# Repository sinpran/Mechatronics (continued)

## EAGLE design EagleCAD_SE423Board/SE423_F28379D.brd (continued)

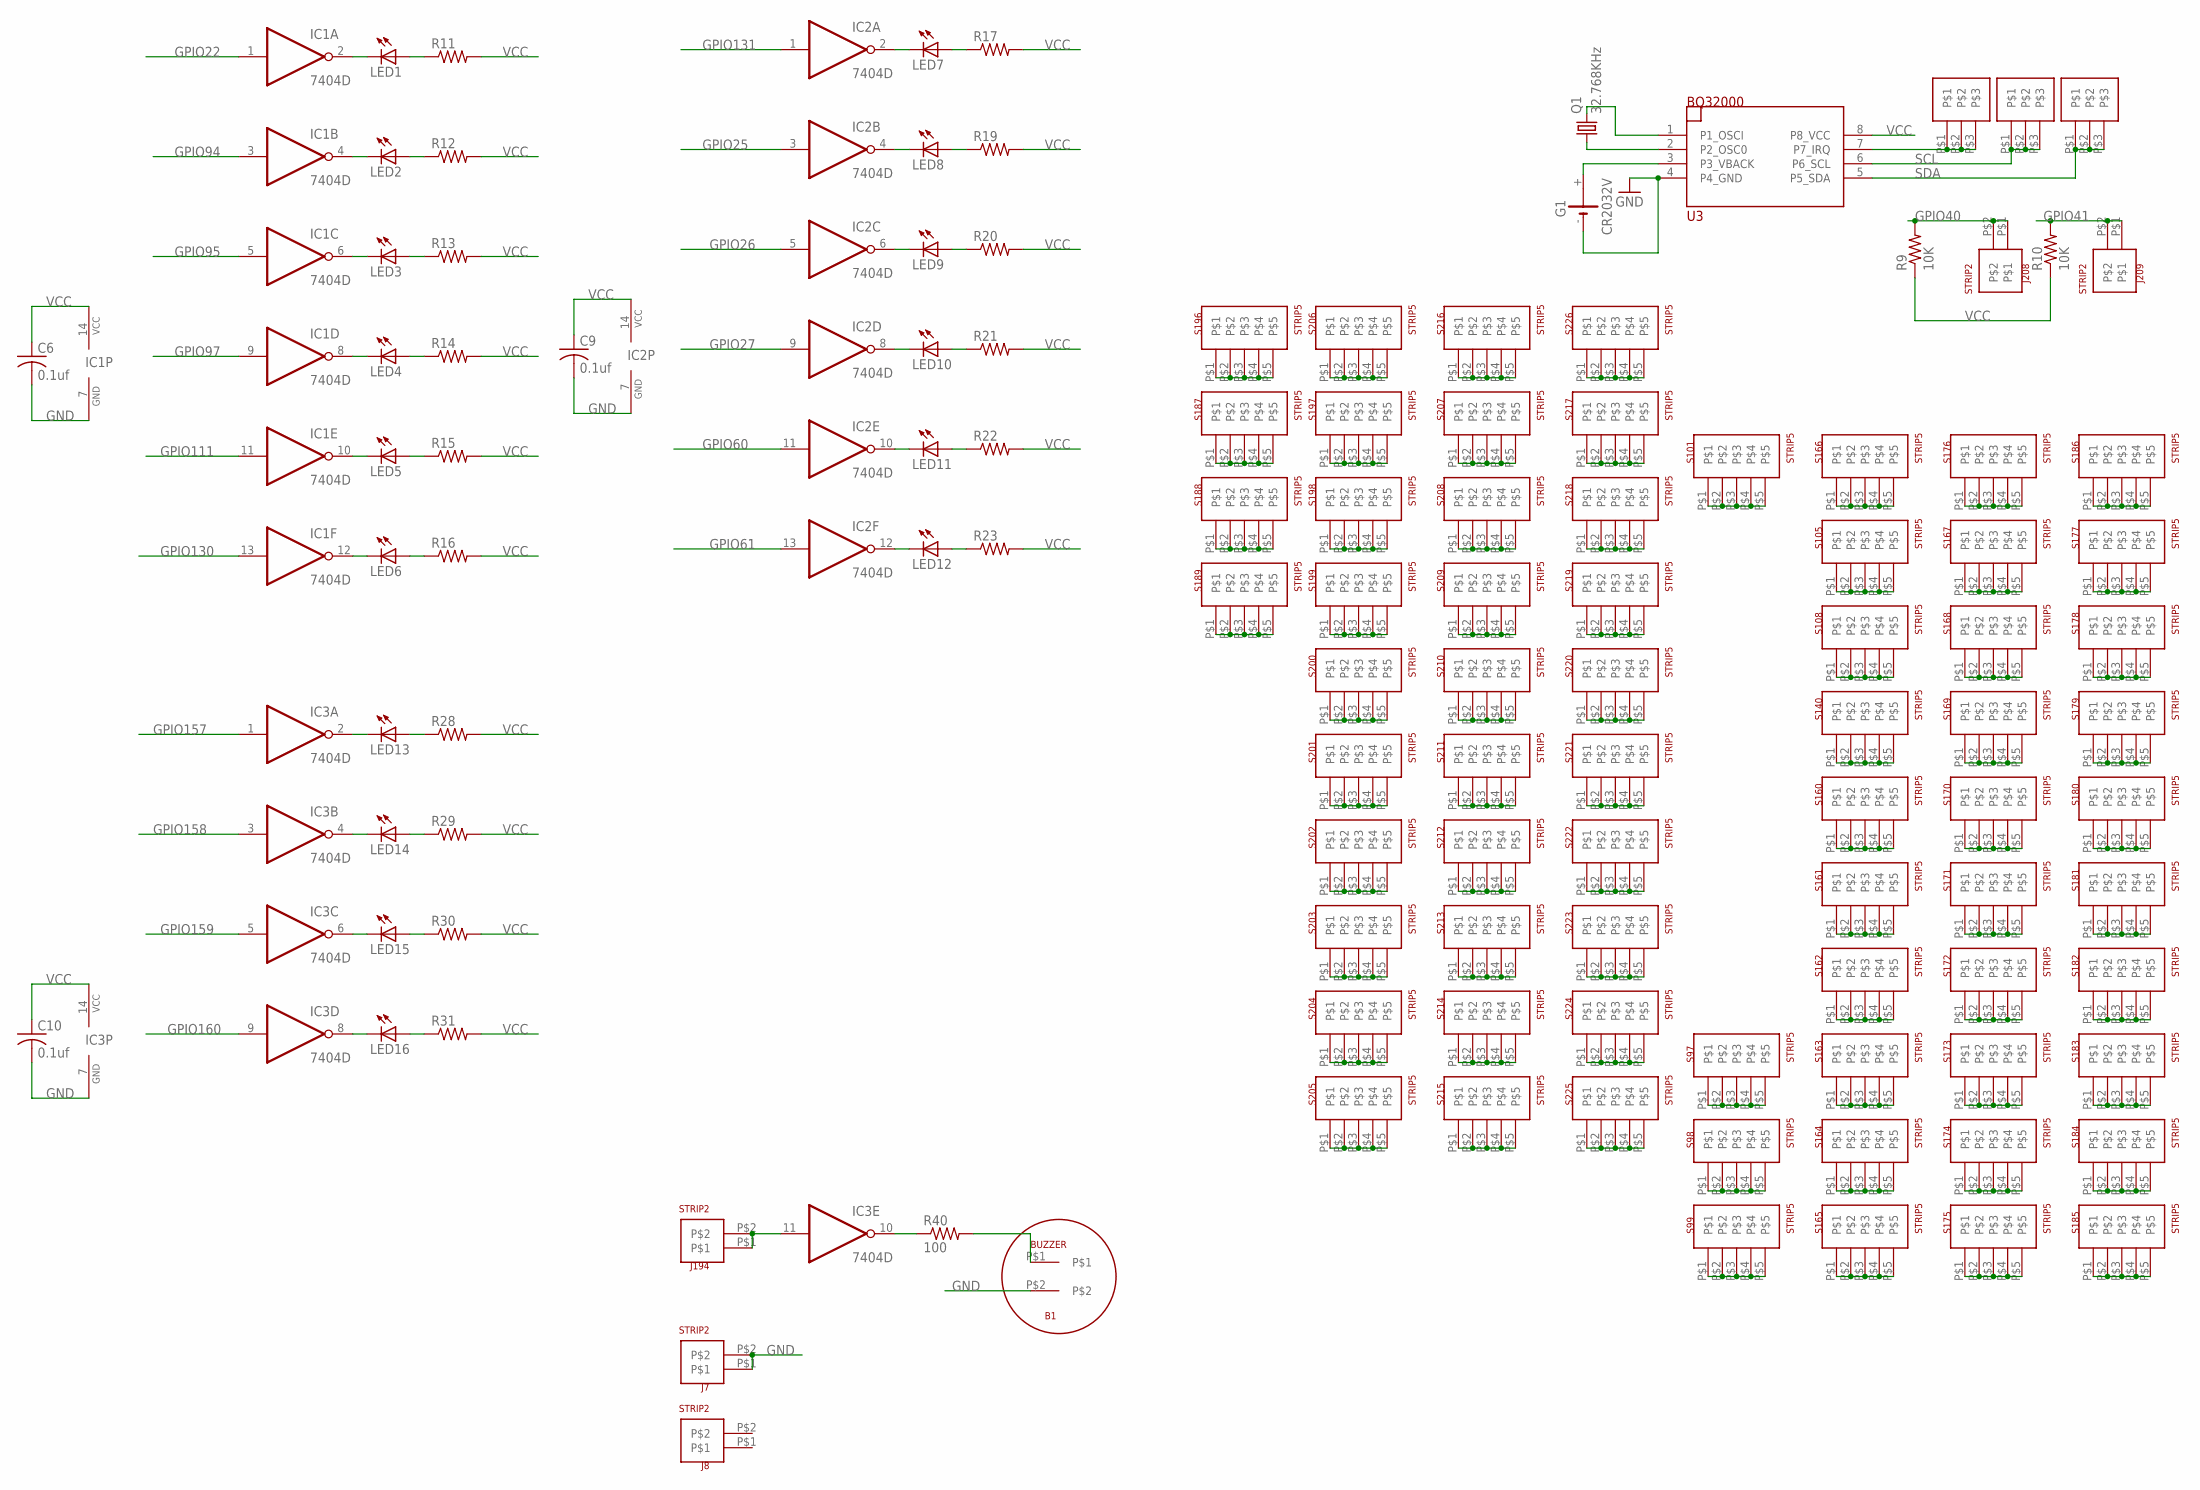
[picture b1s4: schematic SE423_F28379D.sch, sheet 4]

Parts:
B1: BUZZER
C6, C9, C10: 0.1uf; C1206
G1: CR2032V
IC1, IC2, IC3: 7404D; SO14
J1, J2, J3: STRIP3
J7, J8, J194, J208, J209: STRIP2
LED1, LED2, LED3, LED4, LED5, LED6, LED7, LED8, LED9, LED10, LED11, LED12, LED13, LED14, LED15, LED16: LEDCHIPLED_1206; CHIPLED_1206
Q1: 32.768KHz; TC26H
R9, R10: 10K; R1206
R11, R12, R13, R14, R15, R16, R17, R19, R20, R21, R22, R23, R28, R29, R30, R31: R-US_R1206; R1206
R40: 100; R1206
S97, S98, S99, S101, S105, S108, S140, S160, S161, S162, S163, S164, S165, S166, S167, S168, S169, S170, S171, S172, S173, S174, S175, S176, S177, S178, S179, S180, S181, S182, S183, S184, S185, S186, S187, S188, S189, S196, S197, S198, S199, S200, S201, S202, S203, S204, S205, S206, S207, S208, S209, S210, S211, S212, S213, S214, S215, S216, S217, S218, S219, S220, S221, S222, S223, S224, S225, S226: STRIP5
U3: BQ32000; SO08

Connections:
GND: B1.P$2, C6.2, C9.2, C10.2, G1.-, IC1.7 (GND), IC2.7 (GND), IC3.7 (GND), J7.P$1, J7.P$2, U3.4 (P4_GND); also elsewhere on the board
GPIO22: IC1.1 (I); also elsewhere on the board
GPIO25: IC2.3 (I); also elsewhere on the board
GPIO26: IC2.5 (I); also elsewhere on the board
GPIO27: IC2.9 (I); also elsewhere on the board
GPIO40: J208.P$1, J208.P$2, R9.2; also elsewhere on the board
GPIO41: J209.P$1, J209.P$2, R10.2; also elsewhere on the board
GPIO60: IC2.11 (I); also elsewhere on the board
GPIO61: IC2.13 (I); also elsewhere on the board
GPIO94: IC1.3 (I); also elsewhere on the board
GPIO95: IC1.5 (I); also elsewhere on the board
GPIO97: IC1.9 (I); also elsewhere on the board
GPIO111: IC1.11 (I); also elsewhere on the board
GPIO130: IC1.13 (I); also elsewhere on the board
GPIO131: IC2.1 (I); also elsewhere on the board
GPIO157: IC3.1 (I); also elsewhere on the board
GPIO158: IC3.3 (I); also elsewhere on the board
GPIO159: IC3.5 (I); also elsewhere on the board
GPIO160: IC3.9 (I); also elsewhere on the board
unnamed: IC3.10 (O), R40.1
unnamed: B1.P$1, R40.2
unnamed: Q1.1, U3.2 (P2_OSC0)
unnamed: Q1.2, U3.1 (P1_OSCI)
unnamed: J1.P$1, J1.P$2, J1.P$3, U3.7 (P7_IRQ)
unnamed: G1.+, U3.3 (P3_VBACK)
unnamed: IC2.2 (O), LED7.C
unnamed: LED7.A, R17.1
unnamed: IC2.4 (O), LED8.C
unnamed: LED8.A, R19.1
unnamed: IC2.6 (O), LED9.C
unnamed: S97.P$1, S97.P$2, S97.P$3, S97.P$4, S97.P$5
unnamed: S98.P$1, S98.P$2, S98.P$3, S98.P$4, S98.P$5
unnamed: S99.P$1, S99.P$2, S99.P$3, S99.P$4, S99.P$5
unnamed: S101.P$1, S101.P$2, S101.P$3, S101.P$4, S101.P$5
unnamed: S105.P$1, S105.P$2, S105.P$3, S105.P$4, S105.P$5
unnamed: S108.P$1, S108.P$2, S108.P$3, S108.P$4, S108.P$5
unnamed: S140.P$1, S140.P$2, S140.P$3, S140.P$4, S140.P$5
unnamed: S160.P$1, S160.P$2, S160.P$3, S160.P$4, S160.P$5
unnamed: S161.P$1, S161.P$2, S161.P$3, S161.P$4, S161.P$5
unnamed: S162.P$1, S162.P$2, S162.P$3, S162.P$4, S162.P$5
unnamed: S163.P$1, S163.P$2, S163.P$3, S163.P$4, S163.P$5
unnamed: S164.P$1, S164.P$2, S164.P$3, S164.P$4, S164.P$5
unnamed: S165.P$1, S165.P$2, S165.P$3, S165.P$4, S165.P$5
unnamed: S166.P$1, S166.P$2, S166.P$3, S166.P$4, S166.P$5
unnamed: S167.P$1, S167.P$2, S167.P$3, S167.P$4, S167.P$5
unnamed: S168.P$1, S168.P$2, S168.P$3, S168.P$4, S168.P$5
unnamed: S169.P$1, S169.P$2, S169.P$3, S169.P$4, S169.P$5
unnamed: S170.P$1, S170.P$2, S170.P$3, S170.P$4, S170.P$5
unnamed: S171.P$1, S171.P$2, S171.P$3, S171.P$4, S171.P$5
unnamed: S172.P$1, S172.P$2, S172.P$3, S172.P$4, S172.P$5
unnamed: S173.P$1, S173.P$2, S173.P$3, S173.P$4, S173.P$5
unnamed: S174.P$1, S174.P$2, S174.P$3, S174.P$4, S174.P$5
unnamed: S175.P$1, S175.P$2, S175.P$3, S175.P$4, S175.P$5
unnamed: S176.P$1, S176.P$2, S176.P$3, S176.P$4, S176.P$5
unnamed: S177.P$1, S177.P$2, S177.P$3, S177.P$4, S177.P$5
unnamed: S178.P$1, S178.P$2, S178.P$3, S178.P$4, S178.P$5
unnamed: S179.P$1, S179.P$2, S179.P$3, S179.P$4, S179.P$5
unnamed: S180.P$1, S180.P$2, S180.P$3, S180.P$4, S180.P$5
unnamed: S181.P$1, S181.P$2, S181.P$3, S181.P$4, S181.P$5
unnamed: S182.P$1, S182.P$2, S182.P$3, S182.P$4, S182.P$5
unnamed: S183.P$1, S183.P$2, S183.P$3, S183.P$4, S183.P$5
unnamed: S184.P$1, S184.P$2, S184.P$3, S184.P$4, S184.P$5
unnamed: S185.P$1, S185.P$2, S185.P$3, S185.P$4, S185.P$5
unnamed: S186.P$1, S186.P$2, S186.P$3, S186.P$4, S186.P$5
unnamed: S187.P$1, S187.P$2, S187.P$3, S187.P$4, S187.P$5
unnamed: S188.P$1, S188.P$2, S188.P$3, S188.P$4, S188.P$5
unnamed: S189.P$1, S189.P$2, S189.P$3, S189.P$4, S189.P$5
unnamed: S196.P$1, S196.P$2, S196.P$3, S196.P$4, S196.P$5
unnamed: S197.P$1, S197.P$2, S197.P$3, S197.P$4, S197.P$5
unnamed: S198.P$1, S198.P$2, S198.P$3, S198.P$4, S198.P$5
unnamed: S199.P$1, S199.P$2, S199.P$3, S199.P$4, S199.P$5
unnamed: S200.P$1, S200.P$2, S200.P$3, S200.P$4, S200.P$5
unnamed: S201.P$1, S201.P$2, S201.P$3, S201.P$4, S201.P$5
unnamed: S202.P$1, S202.P$2, S202.P$3, S202.P$4, S202.P$5
unnamed: S203.P$1, S203.P$2, S203.P$3, S203.P$4, S203.P$5
unnamed: S204.P$1, S204.P$2, S204.P$3, S204.P$4, S204.P$5
unnamed: S205.P$1, S205.P$2, S205.P$3, S205.P$4, S205.P$5
unnamed: S206.P$1, S206.P$2, S206.P$3, S206.P$4, S206.P$5
unnamed: S207.P$1, S207.P$2, S207.P$3, S207.P$4, S207.P$5
unnamed: S208.P$1, S208.P$2, S208.P$3, S208.P$4, S208.P$5
unnamed: S209.P$1, S209.P$2, S209.P$3, S209.P$4, S209.P$5
unnamed: S210.P$1, S210.P$2, S210.P$3, S210.P$4, S210.P$5
unnamed: S211.P$1, S211.P$2, S211.P$3, S211.P$4, S211.P$5
unnamed: S212.P$1, S212.P$2, S212.P$3, S212.P$4, S212.P$5
unnamed: S213.P$1, S213.P$2, S213.P$3, S213.P$4, S213.P$5
unnamed: S214.P$1, S214.P$2, S214.P$3, S214.P$4, S214.P$5
unnamed: S215.P$1, S215.P$2, S215.P$3, S215.P$4, S215.P$5
unnamed: S216.P$1, S216.P$2, S216.P$3, S216.P$4, S216.P$5
unnamed: S217.P$1, S217.P$2, S217.P$3, S217.P$4, S217.P$5
unnamed: S218.P$1, S218.P$2, S218.P$3, S218.P$4, S218.P$5
unnamed: S219.P$1, S219.P$2, S219.P$3, S219.P$4, S219.P$5
unnamed: S220.P$1, S220.P$2, S220.P$3, S220.P$4, S220.P$5
unnamed: S221.P$1, S221.P$2, S221.P$3, S221.P$4, S221.P$5
unnamed: S222.P$1, S222.P$2, S222.P$3, S222.P$4, S222.P$5
unnamed: S223.P$1, S223.P$2, S223.P$3, S223.P$4, S223.P$5
unnamed: S224.P$1, S224.P$2, S224.P$3, S224.P$4, S224.P$5
unnamed: S225.P$1, S225.P$2, S225.P$3, S225.P$4, S225.P$5
unnamed: S226.P$1, S226.P$2, S226.P$3, S226.P$4, S226.P$5
unnamed: IC1.2 (O), LED1.C
unnamed: LED1.A, R11.1
unnamed: IC1.4 (O), LED2.C
unnamed: LED2.A, R12.1
unnamed: IC1.6 (O), LED3.C
unnamed: LED3.A, R13.1
unnamed: IC1.8 (O), LED4.C
unnamed: LED4.A, R14.1
unnamed: IC1.10 (O), LED5.C
unnamed: LED5.A, R15.1
unnamed: IC1.12 (O), LED6.C
unnamed: LED6.A, R16.1
unnamed: LED9.A, R20.1
unnamed: IC2.8 (O), LED10.C
unnamed: LED10.A, R21.1
unnamed: IC2.10 (O), LED11.C
unnamed: LED11.A, R22.1
unnamed: IC2.12 (O), LED12.C
unnamed: LED12.A, R23.1
unnamed: IC3.2 (O), LED13.C
unnamed: LED13.A, R28.1
unnamed: IC3.4 (O), LED14.C
unnamed: LED14.A, R29.1
unnamed: IC3.6 (O), LED15.C
unnamed: LED15.A, R30.1
unnamed: IC3.8 (O), LED16.C
unnamed: LED16.A, R31.1
unnamed: IC3.11 (I), J194.P$1, J194.P$2
SCL: J2.P$1, J2.P$2, J2.P$3, U3.6 (P6_SCL)
SDA: J3.P$1, J3.P$2, J3.P$3, U3.5 (P5_SDA)
VCC: C6.1, C9.1, C10.1, IC1.14 (VCC), IC2.14 (VCC), IC3.14 (VCC), R9.1, R10.1, R11.2, R12.2, R13.2, R14.2, R15.2, R16.2, R17.2, R19.2, R20.2, R21.2, R22.2, R23.2, R28.2, R29.2, R30.2, R31.2, U3.8 (P8_VCC); also elsewhere on the board

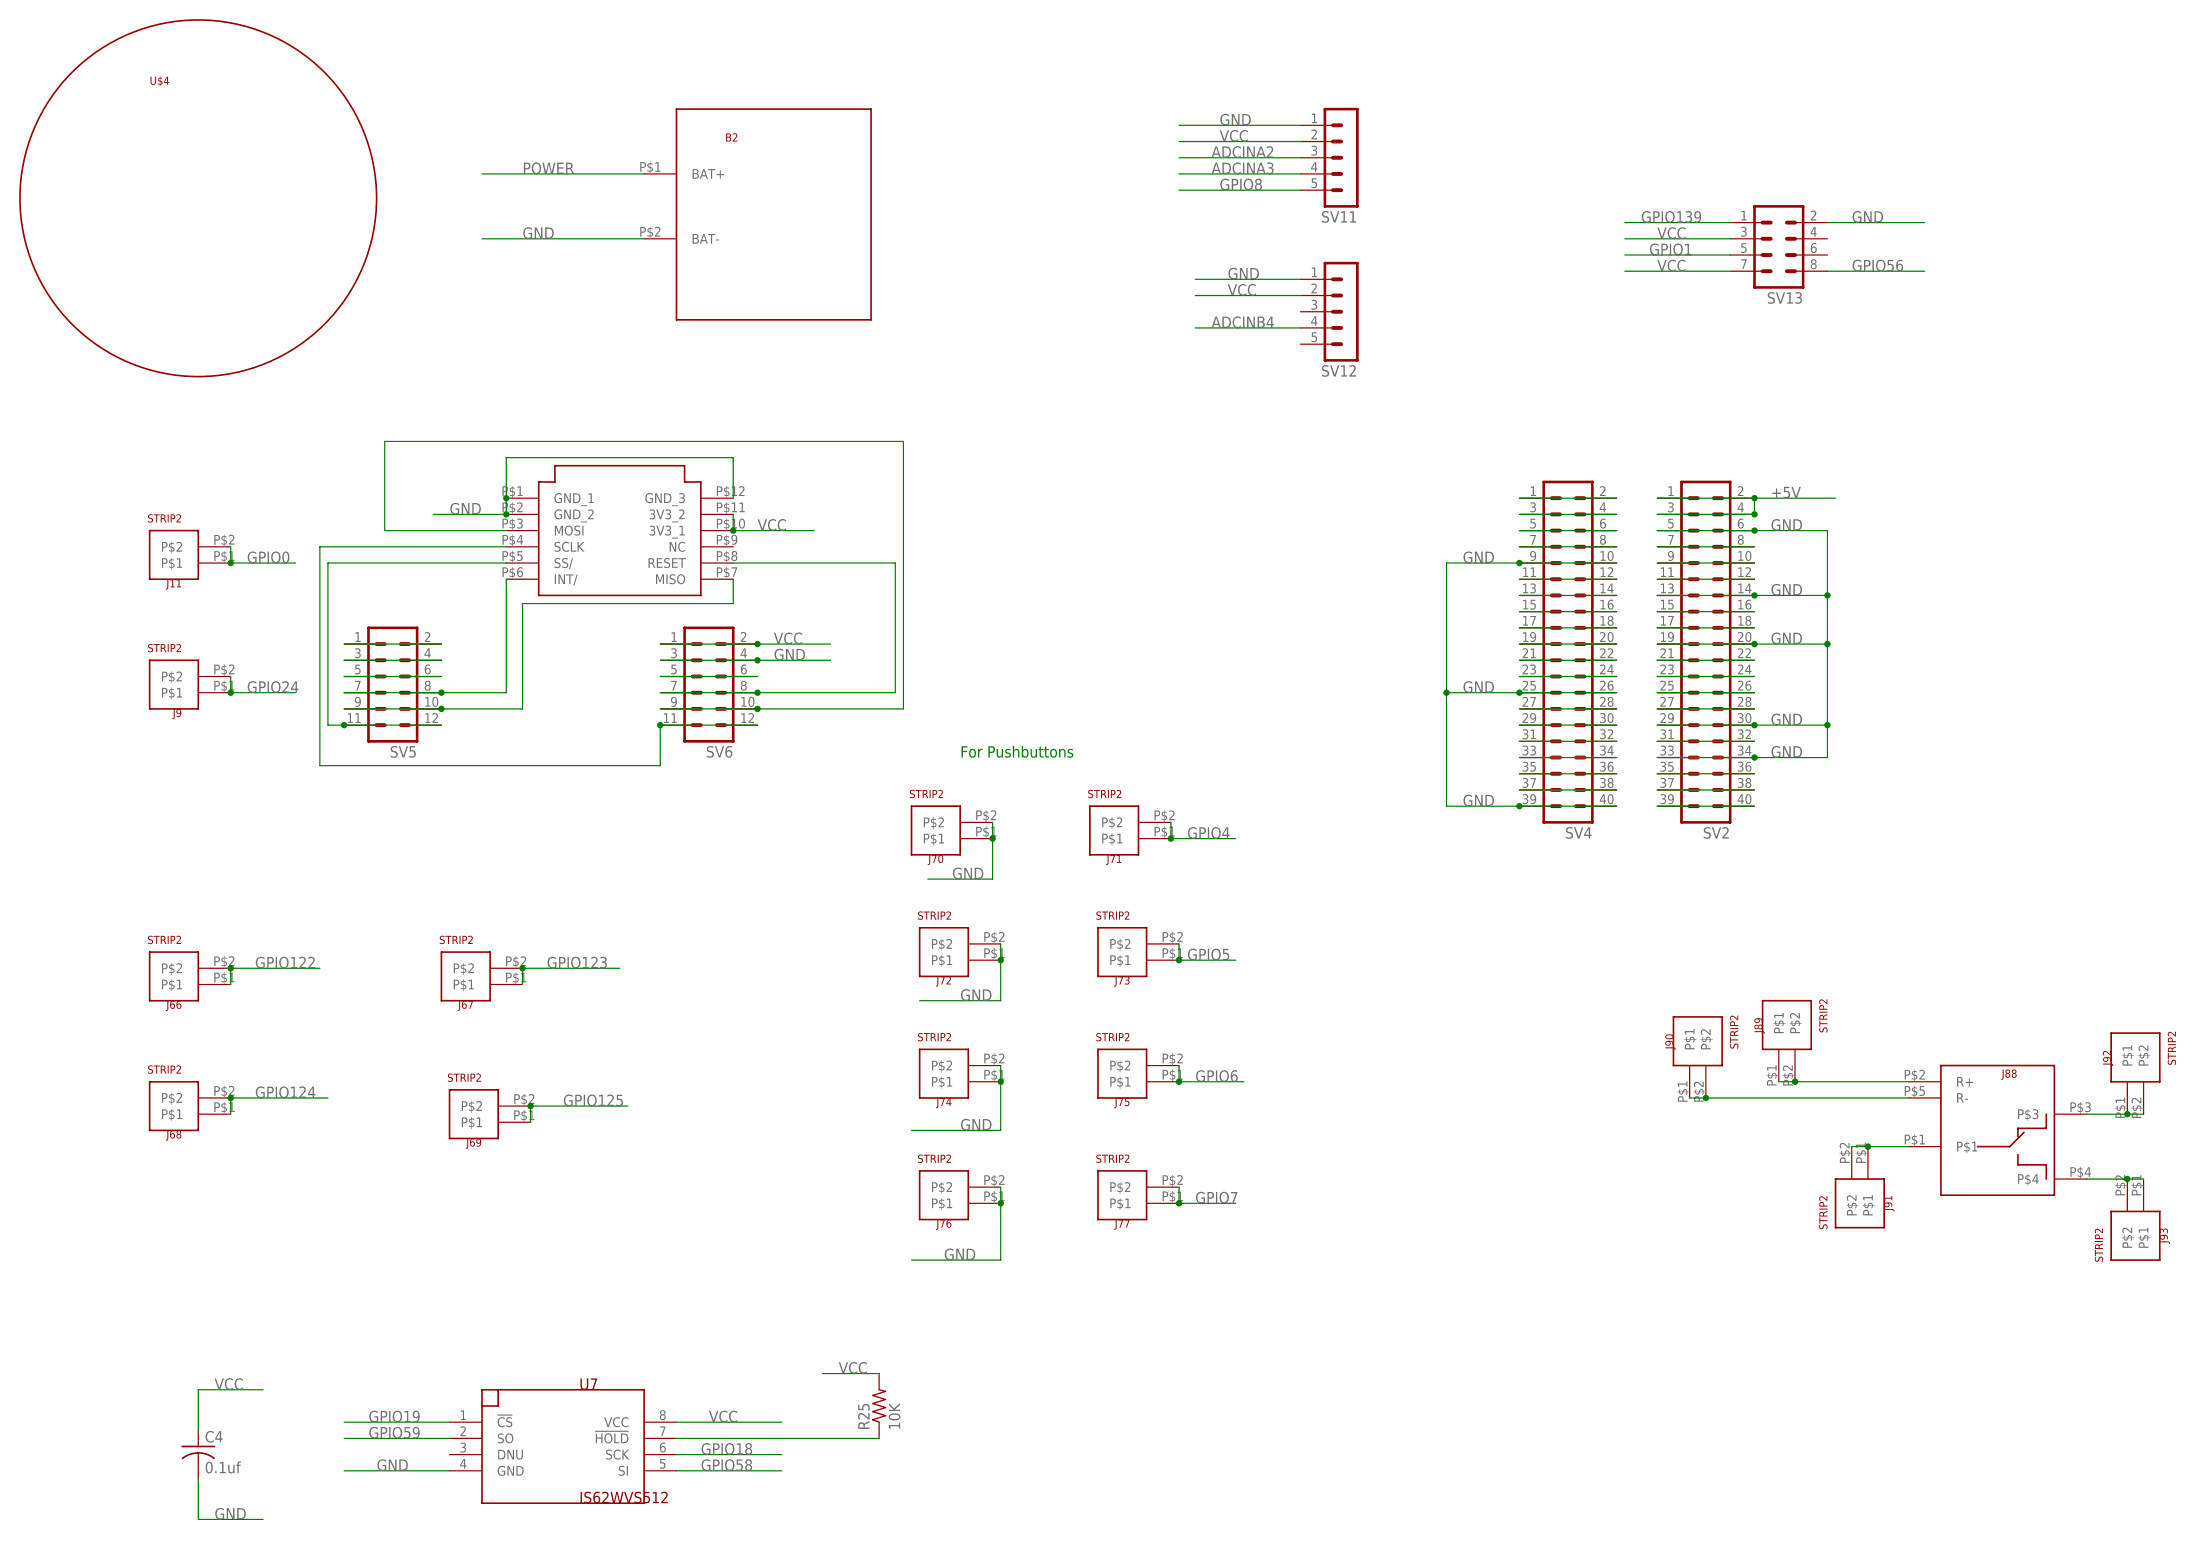
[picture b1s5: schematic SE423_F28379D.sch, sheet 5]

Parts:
B2: BATTERY_4AA_HOLDER
C4: 0.1uf; C1206
ETH1: USR_ES1_W5500
J9, J11, J66, J67, J68, J69, J70, J71, J72, J73, J74, J75, J76, J77, J89, J90, J91, J92, J93: STRIP2
J88: RELAY_JQC-3F_5V
R25: 10K; M1206
SV2, SV4: MA20-2
SV5, SV6: MA06-2
SV11, SV12: MA05-1
SV13: MA04-2
U7: IS62WVS512; SO08
U$4: CASTERWHEEL

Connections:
+5V: SV2.1, SV2.2, SV2.3, SV2.4; also elsewhere on the board
ADCINA2: SV11.3; also elsewhere on the board
ADCINA3: SV11.4; also elsewhere on the board
ADCINB4: SV12.4; also elsewhere on the board
GND: B2.P$2 (BAT-), C4.2, ETH1.P$1 (GND_1), ETH1.P$2 (GND_2), ETH1.P$12 (GND_3), J70.P$1, J70.P$2, J72.P$1, J72.P$2, J74.P$1, J74.P$2, J76.P$1, J76.P$2, SV2.5, SV2.6, SV2.13, SV2.14, SV2.19, SV2.20, SV2.29, SV2.30, SV2.33, SV2.34, SV4.9, SV4.10, SV4.25, SV4.26, SV4.39, SV4.40, SV6.3, SV6.4, SV11.1, SV12.1, SV13.2, U7.4 (GND); also elsewhere on the board
GPIO0: J11.P$1, J11.P$2; also elsewhere on the board
GPIO1: SV13.5; also elsewhere on the board
GPIO4: J71.P$1, J71.P$2; also elsewhere on the board
GPIO5: J73.P$1, J73.P$2; also elsewhere on the board
GPIO6: J75.P$1, J75.P$2; also elsewhere on the board
GPIO7: J77.P$1, J77.P$2; also elsewhere on the board
GPIO8: SV11.5; also elsewhere on the board
GPIO18: U7.6 (SCK); also elsewhere on the board
GPIO19: U7.1 (!CS); also elsewhere on the board
GPIO24: J9.P$1, J9.P$2; also elsewhere on the board
GPIO56: SV13.8; also elsewhere on the board
GPIO58: U7.5 (SI); also elsewhere on the board
GPIO59: U7.2 (SO); also elsewhere on the board
GPIO122: J66.P$1, J66.P$2; also elsewhere on the board
GPIO123: J67.P$1, J67.P$2; also elsewhere on the board
GPIO124: J68.P$1, J68.P$2; also elsewhere on the board
GPIO125: J69.P$1, J69.P$2; also elsewhere on the board
GPIO139: SV13.1; also elsewhere on the board
unnamed: R25.1, U7.7 (!HOLD)
unnamed: SV4.1, SV4.2
unnamed: SV5.1, SV5.2
unnamed: SV5.3, SV5.4
unnamed: SV5.5, SV5.6
unnamed: SV4.3, SV4.4
unnamed: SV4.5, SV4.6
unnamed: SV4.7, SV4.8
unnamed: ETH1.P$6 (INT/), SV5.7, SV5.8
unnamed: SV4.11, SV4.12
unnamed: SV4.13, SV4.14
unnamed: SV4.15, SV4.16
unnamed: SV4.17, SV4.18
unnamed: SV4.19, SV4.20
unnamed: SV4.21, SV4.22
unnamed: SV4.23, SV4.24
unnamed: ETH1.P$7 (MISO), SV5.9, SV5.10
unnamed: SV4.27, SV4.28
unnamed: SV4.29, SV4.30
unnamed: SV4.31, SV4.32
unnamed: SV4.33, SV4.34
unnamed: SV4.35, SV4.36
unnamed: SV4.37, SV4.38
unnamed: ETH1.P$5 (SS/), SV5.11, SV5.12
unnamed: SV2.39, SV2.40
unnamed: SV2.37, SV2.38
unnamed: SV2.35, SV2.36
unnamed: SV2.31, SV2.32
unnamed: SV2.27, SV2.28
unnamed: SV2.25, SV2.26
unnamed: SV2.23, SV2.24
unnamed: SV2.21, SV2.22
unnamed: SV6.5, SV6.6
unnamed: SV2.17, SV2.18
unnamed: SV2.15, SV2.16
unnamed: ETH1.P$8 (RESET), SV6.7, SV6.8
unnamed: SV2.11, SV2.12
unnamed: SV2.9, SV2.10
unnamed: SV2.7, SV2.8
unnamed: ETH1.P$3 (MOSI), SV6.9, SV6.10
unnamed: ETH1.P$4 (SCLK), SV6.11, SV6.12
unnamed: J88.P$2 (R+), J89.P$1, J89.P$2
unnamed: J88.P$5 (R-), J90.P$1, J90.P$2
unnamed: J88.P$1, J91.P$1, J91.P$2
unnamed: J88.P$3, J92.P$1, J92.P$2
unnamed: J88.P$4, J93.P$1, J93.P$2
POWER: B2.P$1 (BAT+); also elsewhere on the board
VCC: C4.1, ETH1.P$10 (3V3_1), ETH1.P$11 (3V3_2), R25.2, SV6.1, SV6.2, SV11.2, SV12.2, SV13.3, SV13.7, U7.8 (VCC); also elsewhere on the board

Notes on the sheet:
For Pushbuttons

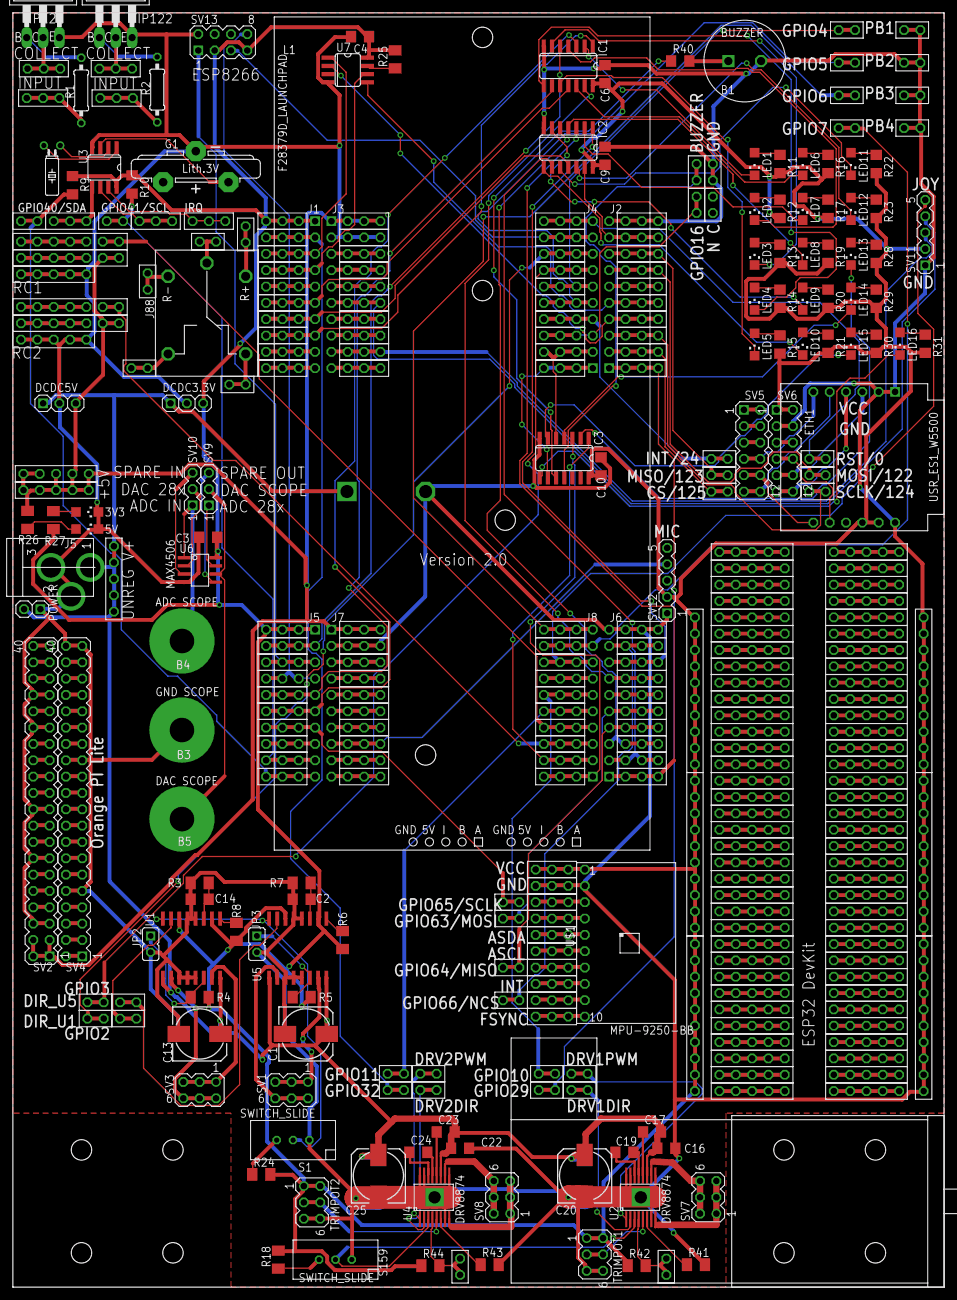
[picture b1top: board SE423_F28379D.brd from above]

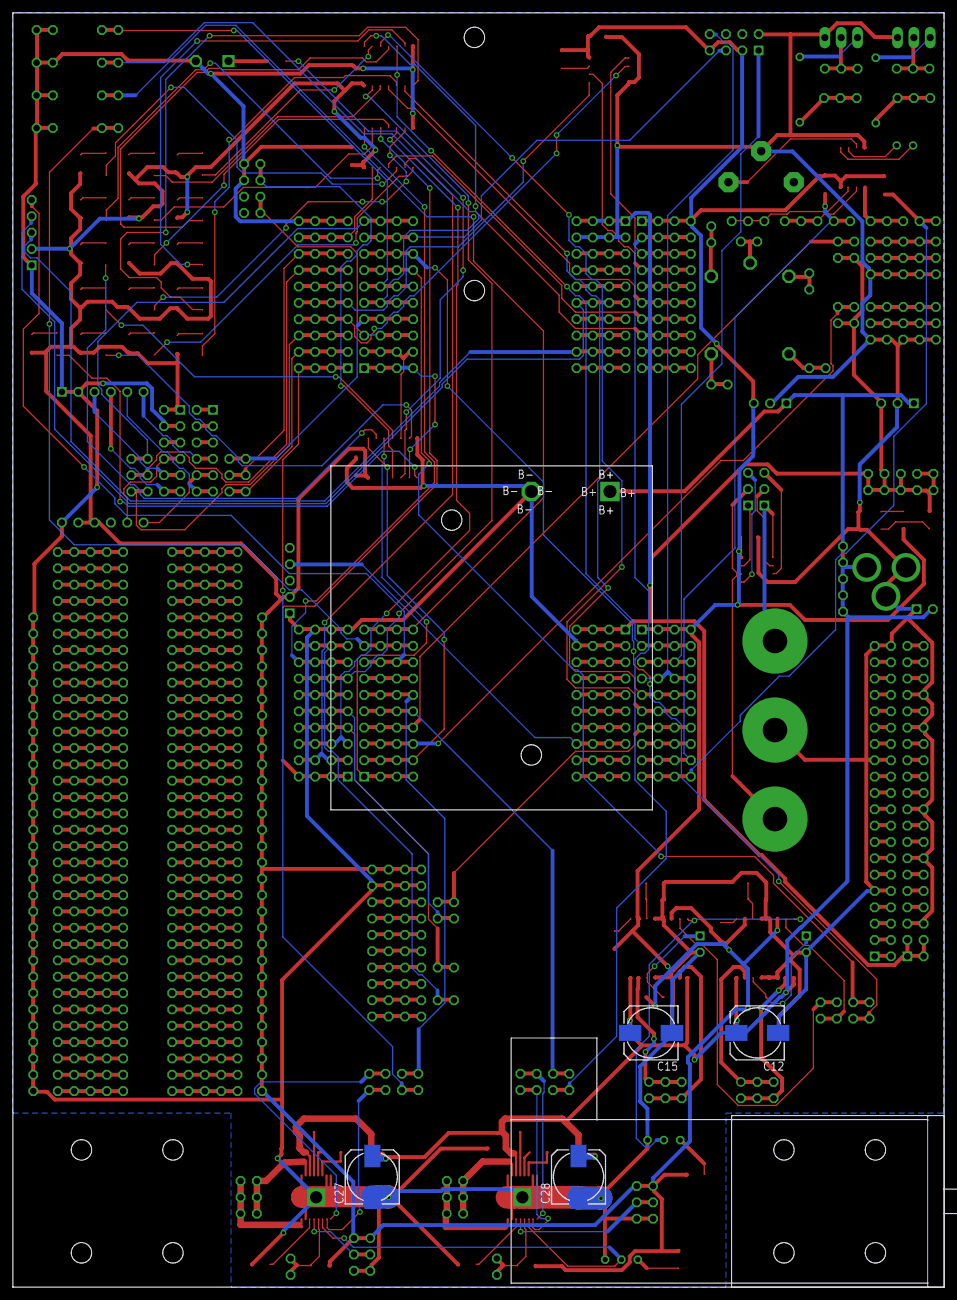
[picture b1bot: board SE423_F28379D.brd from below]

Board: 2 copper layers, 144.8 x 198.1 mm, 351 parts (6 on the bottom side), 293 nets.

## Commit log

2022-01-07 added submissions folder to workspace
